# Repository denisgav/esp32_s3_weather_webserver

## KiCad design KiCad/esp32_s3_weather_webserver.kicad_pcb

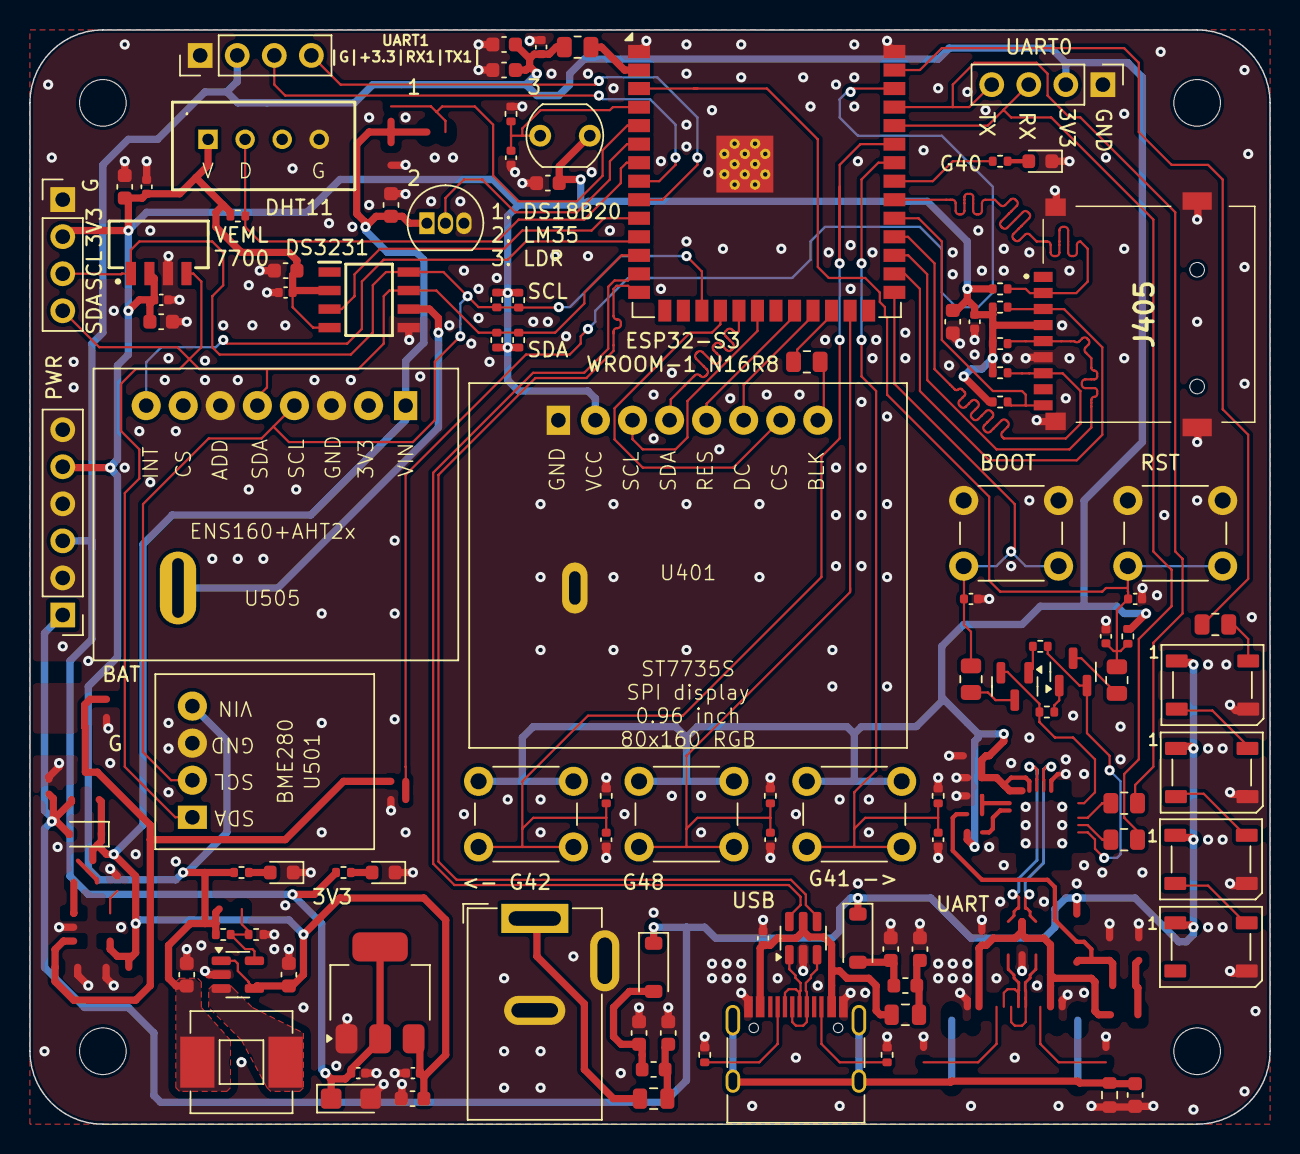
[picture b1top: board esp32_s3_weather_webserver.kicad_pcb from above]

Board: 4 copper layers, 85.0 x 75.0 mm, 110 parts (1 on the bottom side), 65 nets.

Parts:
BT501: Battery_Cell; MPD_BC2032-E2
C201, C402, C407, C501, C503, C506, C507, C509: 10uF; C_0603_1608Metric
C202, C203, C304, C403, C404, C405, C406, C408, C502, C504, C508, C510, C511, C512, C513: 100nF; C_0402_1005Metric
C204: 22uF_P; CP_EIA-3216-18_Kemet-A
C205, C206, C212, C213: 2.2uF; C_0603_1608Metric
C209, C210, C401: 22uF; C_0603_1608Metric
C305: 1nF; C_0603_1608Metric
D201, D203: 1N5819HW-7-F; D_SOD-123
D204: PMEG1030EJ,115; D_SOD-323F
D206, D207, D208, D209: WS2812B; LED_WS2812B_PLCC4_5.0x5.0mm_P3.2mm
D210, D211, D212: LED; LED_0603_1608Metric
F201, F203: 3A; Fuse_0805_2012Metric
FB201, FB203: 120R; Fuse_0603_1608Metric
H101, H102, H103, H104: MountingHole; MountingHole_3.2mm_M3
IC401: ESP32-S3-WROOM-1-N16R8; ESP32S3WROOM1N16R8
IC501: VEML7700-TT; VEML7700
IC502: DS3231MZ+TRL; SOIC127P600X175-8N
J201: Barrel_Jack_Switch_Pin3Ring; BarrelJack_GCT_DCJ200-10-A_Horizontal
J302: USB_C_Receptacle_USB2.0; USB_C_Receptacle_HRO_TYPE-C-31-M-12
J401, J402, J403: Conn_01x04_Pin; PinHeader_1x04_P2.54mm_Vertical
J404: Conn_01x06_Pin; PinHeader_1x06_P2.54mm_Vertical
J405: TF-01A; TF01A
L201: 15uH; MWSA0603S
Q401, Q402: SS8050; SOT-23
R201: 100kR; R_0402_1005Metric
R202: 22kR; R_0402_1005Metric
R206, R401, R402, R403, R405, R408, R409: 0R; R_0805_2012Metric
R207, R208, R209: 510R; R_0402_1005Metric
R305, R306, R505: 5k1R; R_0402_1005Metric
R308: DNP, 1MR; R_0603_1608Metric
R404, R406, R407, R410, R411, R412, R413, R414, R501, R502, R503, R506, R507, R508, R509, R510: 10kR; R_0402_1005Metric
RLO501: LDR; R_LDR_5.1x4.3mm_P3.4mm_Vertical
SW401, SW402, SW501, SW502, SW503: SW_PUSH_6mm_H5mm
U201: AMS1117-3.3; SOT-223-3_TabPin2
U202: TLV62569DBV; SOT-23-5
U302: USBLC6-2SC6; SOT-23-6
U401: ST7735S
U501: BME280
U503: LM35-LP; TO-92_Inline
U504: DHT11
U505: ENS160+AHT2x

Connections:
+3V3: C203.1, C204.1, C401.1, C402.1, C403.1, J401.2, J402.2, J404.3, R207.2, R401.1, R404.2, SW501.1, SW501.4, SW502.1, SW502.4, SW503.1, SW503.4, U201.2 (VO)
+3V3_ESP32: IC401.2 (3V3), R401.2
+3V3_PER: C210.1, C407.1, C408.1, C501.1, C503.1, C504.1, C507.1, C508.1, C509.1, C510.1, IC501.2 (VDD), IC502.2 (VCC), IC502.4 (~RST), J403.2, J404.5, J405.4 (VDD), L201.2, R201.2, R208.2, R410.2, R411.2, R412.2, R413.2, R414.2, R502.2, R503.2, R505.1, R506.2, R507.2, RLO501.2, U401.2 (VCC), U501.4 (VIN), U504.1 (VDD)
+5V: D201.1 (K), D203.1 (K), D204.2 (A), D206.1 (VDD), D207.1 (VDD), D208.1 (VDD), D209.1 (VDD), J404.1
+5V_IN: F201.1, J201.1
+5V_IN_FILT: C206.1, D201.2 (A), FB201.1
+5V_IN_FUSE: C205.1, F201.2, FB201.2
+VCC_USB_FILT: C213.1, D203.2 (A), FB203.1
+VCC_USB_FUSE: C212.1, F203.2, FB203.2
/[2] Power/BUCK_FB: R201.1, R202.2, U202.5 (FB)
/[2] Power/BUCK_SW: L201.1, U202.3 (SW)
/[2] Power/LED_3V3_A: D210.2 (A), R207.1
/[2] Power/LED_3V3_PER_A: D211.2 (A), R208.1
/[2] Power/LED_ONBOARD_A: D212.2 (A), R209.1
/[3] USB/USB_CONN_CC1: J302.A5 (CC1), R305.1
/[3] USB/USB_CONN_CC2: J302.B5 (CC2), R306.1
/[3] USB/USB_CONN_D+: J302.A6 (D+), J302.B6 (D+), U302.3 (I/O2)
/[3] USB/USB_CONN_D-: J302.A7 (D-), J302.B7 (D-), U302.1 (I/O1)
/[4] ESP32 S3/CHIP_PU: C404.1, C405.1, IC401.3 (EN), R404.1, R405.2, SW401.1, SW401.4
/[4] ESP32 S3/IO0_BTN: C406.1, IC401.27 (IO0), R408.2, SW402.1, SW402.4
/[4] ESP32 S3/RXD0: IC401.36 (RXD0), J402.3, R403.2
/[4] ESP32 S3/TXD0: IC401.37 (TXD0), J402.4, R402.2
/[5] Peripherals/VBAT: BT501.1 (+), IC502.6 (VBAT)
DHT11: IC401.7 (IO7), R505.2, U504.2 (DATA)
DS3231_INT: IC401.10 (IO17), IC502.3 (~INT/SQW)
DTR: Q402.2 (E), R406.1
ENS160_INT: IC401.11 (IO18), U505.8 (INT)
FSPI_MISO: IC401.30 (IO37), J405.7 (D0/DO), R410.1
FSPI_MOSI: IC401.28 (IO35), J405.3 (CMD/DI), R411.1
FSPI_SCK: IC401.29 (IO36), J405.5 (CLK/SCLK), R412.1
FSPI_SS: IC401.32 (IO39), J405.2 (D3/CS), R413.1
GND: BT501.2 (-), C201.2, C202.2, C203.2, C204.2, C205.2, C206.2, C209.2, C210.2, C212.2, C213.2, C304.2, C305.2, C401.2, C402.2, C403.2, C404.2, C405.2, C406.2, C407.2, C408.2, C501.2, C502.2, C503.2, C504.2, C506.2, C507.2, C508.2, C509.2, C510.2, C511.2, C512.2, C513.2, D206.3 (VSS), D207.3 (VSS), D208.3 (VSS), D209.3 (VSS), D210.1 (K), D211.1 (K), D212.1 (K), IC401.1 (GND_1), IC401.40 (GND_2), IC401.41 (GND_3), IC501.3 (GND), IC502.5 (GND), J201.2, J201.3, J302.A1 (GND), J302.A12 (GND), J302.B1 (GND), J302.B12 (GND), J401.1, J402.1, J403.1, J404.2, J404.4, J404.6, J405.6 (VSS), J405.MP1, J405.MP2, J405.MP3, J405.MP4, R202.1, R305.2, R306.2, R308.2, R501.2, R508.1, R509.1, R510.1, SW401.2, SW401.3, SW402.2, SW402.3, U201.1 (GND), U202.2 (GND), U302.2 (GND), U401.1 (GND), U501.3 (GND), U503.3 (GND), U504.4 (GND), U505.3 (GND), U505.6 (ADD)
GNDPWR: C305.1, J302.S1 (SHIELD), R308.1
HSPI_MOSI: IC401.19 (IO11), U401.4 (SDA)
HSPI_SCK: IC401.20 (IO12), U401.3 (SCL)
HSPI_SS: IC401.18 (IO10), U401.7 (CS)
I2C_SCL: IC401.17 (IO9), IC501.1 (SCL), IC502.8 (SCL), J403.3, R502.1, R507.1, U501.2 (SCL), U505.4 (SCL)
I2C_SDA: IC401.12 (IO8), IC501.4 (SDA), IC502.7 (SDA), J403.4, R503.1, R506.1, U501.1 (SDA), U505.5 (SDA)
LDR: C502.1, IC401.4 (IO4), R501.1, RLO501.1
LM35: IC401.6 (IO6), U503.2 (V_{OUT})
unnamed: D206.4 (DIN), R206.1
unnamed: D206.2 (DOUT), D207.4 (DIN)
unnamed: D207.2 (DOUT), D208.4 (DIN)
unnamed: D208.2 (DOUT), D209.4 (DIN)
unnamed: Q401.1 (B), R406.2
unnamed: Q401.3 (C), R405.1
unnamed: Q402.1 (B), R407.2
unnamed: Q402.3 (C), R408.1
unnamed: R409.1, U401.8 (BLK)
ONBOARD_LED: IC401.33 (IO40), R209.2
RTS: Q401.2 (E), R407.1
RXD1: IC401.8 (IO15), J401.3
SD_CD: IC401.31 (IO38), J405.CD1, R414.1
TFT_BLK: IC401.24 (IO47), R409.2
TFT_DC: IC401.23 (IO21), U401.6 (DC)
TFT_RES: IC401.22 (IO14), U401.5 (RES)
TXD1: IC401.9 (IO16), J401.4
USB_D+: IC401.14 (IO20), U302.4 (I/O2)
USB_D-: IC401.13 (IO19), U302.6 (I/O1)
USB_VBUS: C304.1, F203.1, J302.A4 (VBUS), J302.A9 (VBUS), J302.B4 (VBUS), J302.B9 (VBUS), U302.5 (VBUS)
USR_BTN: C511.1, IC401.25 (IO48), R508.2, SW501.2, SW501.3
USR_BTN_LEFT: C512.1, IC401.35 (IO42), R509.2, SW502.2, SW502.3
USR_BTN_RIGHT: C513.1, IC401.34 (IO41), R510.2, SW503.2, SW503.3
VIN: C201.1, C202.1, C209.1, C506.1, D204.1 (K), U201.3 (VI), U202.1 (EN), U202.4 (VIN), U503.1 (+V_{S}), U505.1 (VIN)
WS2812_RGB_STRIP: IC401.39 (IO1), R206.2

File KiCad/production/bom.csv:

Designator,Footprint,Quantity,Value,LCSC Part #
BT501,MPD_BC2032-E2,1,Battery_Cell,
"C201, C402, C407, C501, C503, C506, C507, C509",0603,8,10uF,
"C202, C203, C304, C403, C404, C405, C406, C408, C502, C504, C508, C510, C511, C512, C513",0402,15,100nF,
C204,CP_EIA-3216-18_Kemet-A,1,22uF_P,
"C205, C206, C212, C213",0603,4,2.2uF,
"C209, C210, C401",0603,3,22uF,
C305,0603,1,1nF,
"D201, D203",D_SOD-123,2,1N5819HW-7-F,
D204,D_SOD-323F,1,"PMEG1030EJ,115",
"D206, D207, D208, D209",LED_WS2812B_PLCC4_5.0x5.0mm_P3.2mm,4,WS2812B,
"D210, D211, D212",0603,3,LED,
"F201, F203",0805,2,3A,
"FB201, FB203",0603,2,120R,
"H101, H102, H103, H104",MountingHole_3.2mm_M3,4,MountingHole,
IC401,ESP32S3WROOM1N16R8,1,ESP32-S3-WROOM-1-N16R8,
IC501,VEML7700,1,VEML7700-TT,
IC502,SOIC127P600X175-8N,1,DS3231MZ+TRL,
J201,BarrelJack_GCT_DCJ200-10-A_Horizontal,1,Barrel_Jack_Switch_Pin3Ring,
J302,USB_C_Receptacle_HRO_TYPE-C-31-M-12,1,USB_C_Receptacle_USB2.0,
"J401, J402, J403",PinHeader_1x04_P2.54mm_Vertical,3,Conn_01x04_Pin,
J404,PinHeader_1x06_P2.54mm_Vertical,1,Conn_01x06_Pin,
J405,TF01A,1,TF-01A,
L201,MWSA0603S,1,15uH,
"Q401, Q402",SOT-23,2,SS8050,
R201,0402,1,100kR,
R202,0402,1,22kR,
"R206, R401, R402, R403, R405, R408, R409",0805,7,0R,
"R207, R208, R209",0402,3,510R,
"R305, R306, R505",0402,3,5k1R,
R308,0603,1,"DNP, 1MR",
"R404, R406, R407, R410, R411, R412, R413, R414, R501, R502, R503, R506, R507, R508, R509, R510",0402,16,10kR,
RLO501,R_LDR_5.1x4.3mm_P3.4mm_Vertical,1,LDR,
"SW401, SW402, SW501, SW502, SW503",SW_PUSH_6mm_H5mm,5,~,
U201,SOT-223-3_TabPin2,1,AMS1117-3.3,
U202,SOT-23-5,1,TLV62569DBV,
U302,SOT-23-6,1,USBLC6-2SC6,
U401,ST7735S,1,~,
U501,BME280,1,~,
U503,TO-92_Inline,1,LM35-LP,
U504,DHT11,1,DHT11,
U505,ENS160+AHT2x,1,~,

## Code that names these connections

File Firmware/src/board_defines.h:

#pragma once
// SPI	        |MOSI	    |MISO	    |CLK	    |CS
// HSPI (SPI 1)	|GPIO 11	|GPIO 13	|GPIO 12	|GPIO 10
// FSPI (SPI 0)	|GPIO 35	|GPIO 37	|GPIO 36	|GPIO 39

// SD pins
// SD -> SPI
// D0 -> DO
// D1 -> X
// D2 -> X
// D3 -> CS
// CMD -> DI
// CLK -> SCLK

//--------------------------
// SPI buses
//--------------------------
const int HSPI_SS_PIN    = 10;
const int HSPI_MOSI_PIN  = 11;
const int HSPI_SCK_PIN   = 12;
const int HSPI_MISO_PIN  = 13;

const int FSPI_SS_PIN    = 39;
const int FSPI_MOSI_PIN  = 35;
const int FSPI_SCK_PIN   = 36;
const int FSPI_MISO_PIN  = 37;
//--------------------------

//--------------------------
// I2C bus
//--------------------------
const int I2C_SDA_PIN  = 8;
const int I2C_SCL_PIN  = 9;
//--------------------------

//--------------------------
// UART1 bus
//--------------------------
const int UART1_RXD_PIN  = 15;
const int UART1_TXD_PIN  = 16;
//--------------------------

//--------------------------
// Peripherals
//--------------------------
const int WS2812_RGB_STRIP_PIN = 1;
const int LDR_PIN              = 4;
const int DS18B20_PIN          = 5;
const int LM35_PIN             = 6;
const int DHT11_PIN            = 7;

const int DS3231_INT_PIN       = 17;
const int ENS160_INT_PIN       = 18;

const int USR_BTN_PIN          = 48;
const int USR_BTN_LEFT_PIN     = 42;
const int USR_BTN_RIGHT_PIN    = 41;
const int USR_ONBOARD_LED_PIN  = 40;

const int SD_CD                = 38;
//--------------------------

//--------------------------
// TFT Display
//--------------------------
const int TFT_SCL_PIN  = HSPI_SCK_PIN;  // SPI clock signal
const int TFT_SDA_PIN  = HSPI_MOSI_PIN; // Serial data input pin sda
const int TFT_CS_PIN   = HSPI_SS_PIN; // LCD chip select signal, for SPI protocol
const int TFT_DC_PIN   = 21; // Data selection signal
const int TFT_RES_PIN  = 14; // Reset pin
const int TFT_BLK_PIN  = 47; // Back light
//--------------------------

//--------------------------
// SD SPI pins option
//--------------------------
const int SD_SCK_PIN  = FSPI_SCK_PIN;
const int SD_MISO_PIN = FSPI_MISO_PIN;
const int SD_MOSI_PIN = FSPI_MOSI_PIN;
const int SD_CS_PIN   = FSPI_SS_PIN; /* D3 */
//--------------------------

//--------------------------
// SD MMC pins option
//--------------------------
const int SD_MMC_CLK_PIN = FSPI_SCK_PIN;  // SCK OTG
const int SD_MMC_CMD_PIN = FSPI_MOSI_PIN; // MOSI OTG
const int SD_MMC_D0_PIN  = FSPI_MISO_PIN; // MISO OTG
//--------------------------

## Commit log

2025-08-28 SD card test initial commit
2025-08-29 Connect TFT display and SD card
2025-08-29 Add RTC to the sketch
2025-08-29 Started to add async webserver
2025-08-30 Non operational web server
2025-08-30 Not operational web server
2025-08-31 Fix display initialization
2025-09-05 Add KiCad project
2025-09-05 USB scheme
2025-09-05 Update power scheme
2025-09-06 Update ESP32 Scheme
2025-09-06 Add SD card to scheme
2025-09-06 Add BME280
2025-09-06 Add DS3231
2025-09-06 Add analog sensors
2025-09-07 First scheme version
2025-09-08 Firmware refactoring. Beginning
2025-09-09 Update BME280 Scheme, Add more sensors to firmware
2025-09-09 Add UART pin header
2025-09-09 Add multisensor wrapper
2025-09-09 Add simple web server
2025-09-10 Site updates
2025-09-10 all sensors on web page
2025-09-10 Add JSON library
2025-09-10 Scan WiFi networks
2025-09-11 Remove 3V3A power chain
2025-09-11 Add sensor footprints
2025-09-11 BOM updates
2025-09-12 BOM updates. First layout
2025-09-12 Layout updates
2025-09-13 PCB layout updates
2025-09-13 PCB layout improvements
2025-09-14 Simple routing
2025-09-14 SPI signals routing
2025-09-15 Simple signal routing
2025-09-16 Signals routing
2025-09-16 Signal routing
2025-09-16 Fix USB signal routing
2025-09-18 Fix DRC
2025-09-18 Temperature sensor placement update
2025-09-18 Silk Screen updates
2025-09-18 Add VEML7700 to the firmware
2025-09-18 Update pin defines
2025-09-18 JSON response improvements
2025-09-18 Add RTC to the web page
2025-09-19 Add good/bad value indication
2025-09-19 Set RTC time from the web page
2025-09-19 tooltip fixes
2025-09-19 Add WiFi management
2025-09-20 Add battery connector and charger
2025-09-20 Connect VBAT to ADC input to measure battery voltage
2025-09-20 Use tantalum capacitor with AMS. Add basic output to TFT.
2025-09-20 VBAT decoupling capacitor
2025-09-21 Production files prepare
2025-09-21 Update BOM file
2025-09-23 LCD updates
2025-09-23 Fix display artifacts
2025-10-02 Add Wifi info to LCD
2025-10-02 add ds18b20 to firmware
2025-10-04 Java script updates
2026-01-04 Remove broken scheme parts
